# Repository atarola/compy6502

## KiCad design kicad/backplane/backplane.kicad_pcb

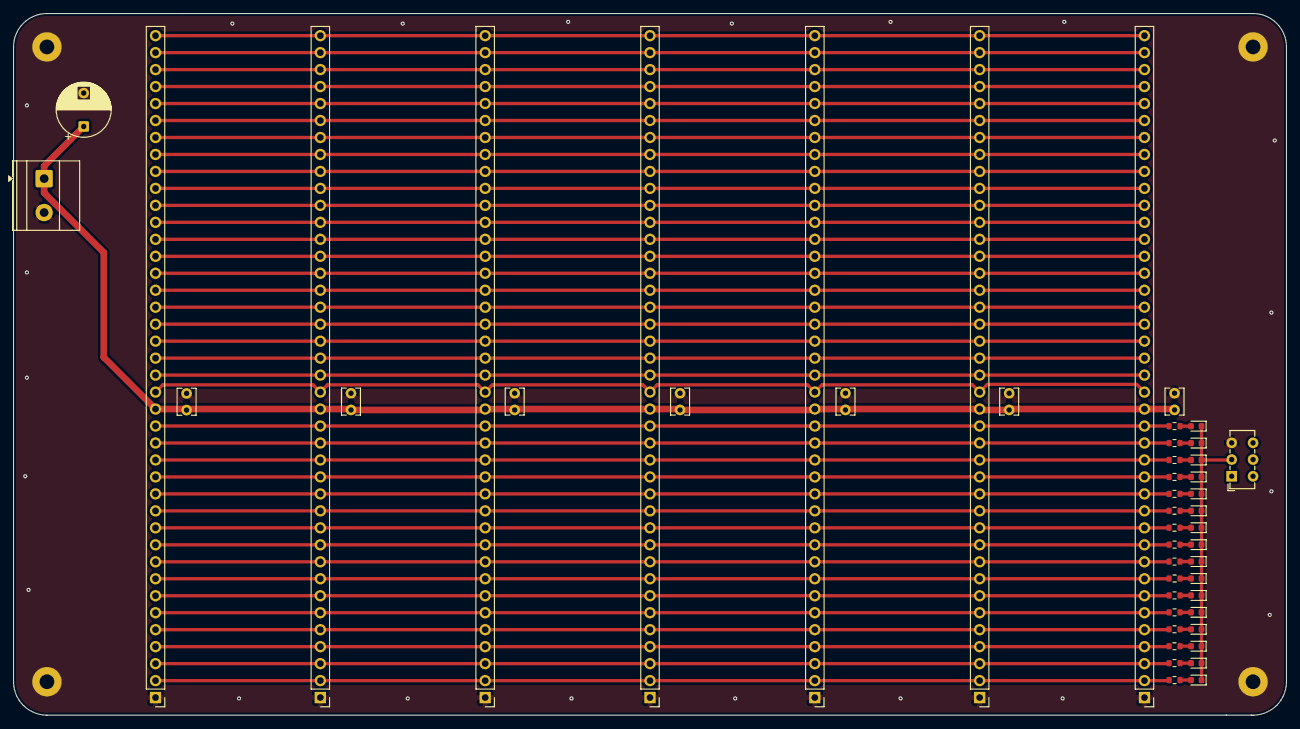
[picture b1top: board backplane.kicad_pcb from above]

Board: 2 copper layers, 190.5 x 105.0 mm, 53 parts (0 on the bottom side), 57 nets.

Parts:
C1: 100u; CP_Radial_D8.0mm_P5.00mm
C2, C3, C4, C5, C6, C7, C8: 0.1u; C_Disc_D3.8mm_W2.6mm_P2.50mm
D1, D2, D3, D4, D5, D6, D7, D8, D9, D10, D11, D12, D13, D14, D15, D16: LED_0603_1608Metric
H1, H2, H3, H4: MountingHole_Pad; MountingHole_2.2mm_M2_Pad
J1, J2, J3, J4, J5, J6, J7: Board Connector; PinHeader_1x40_P2.54mm_Vertical
J9: Screw_Terminal_01x02; TerminalBlock_Phoenix_MKDS-1,5-2-5.08_1x02_P5.08mm_Horizont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
R1, R2, R3, R4, R5, R6, R7, R8, R9, R10, R11, R12, R13, R14, R15, R16: 10k; R_0603_1608Metric
SW1: SW_SPDT; SW_E-Switch_EG1271_SPDT

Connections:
5V: C1.1, C2.1, C3.1, C4.1, C5.1, C6.1, C7.1, C8.1, J1.18, J2.18, J3.18, J4.18, J5.18, J6.18, J7.18, J9.1
/LED_GND: D1.1 (K), D2.1 (K), D3.1 (K), D4.1 (K), D5.1 (K), D6.1 (K), D7.1 (K), D8.1 (K), D9.1 (K), D10.1 (K), D11.1 (K), D12.1 (K), D13.1 (K), D14.1 (K), D15.1 (K), D16.1 (K), SW1.2 (B)
A0: J1.17, J2.17, J3.17, J4.17, J5.17, J6.17, J7.17, R16.1
A1: J1.16, J2.16, J3.16, J4.16, J5.16, J6.16, J7.16, R15.1
A2: J1.15, J2.15, J3.15, J4.15, J5.15, J6.15, J7.15, R14.1
A3: J1.14, J2.14, J3.14, J4.14, J5.14, J6.14, J7.14, R13.1
A4: J1.13, J2.13, J3.13, J4.13, J5.13, J6.13, J7.13, R12.1
A5: J1.12, J2.12, J3.12, J4.12, J5.12, J6.12, J7.12, R11.1
A6: J1.11, J2.11, J3.11, J4.11, J5.11, J6.11, J7.11, R10.1
A7: J1.10, J2.10, J3.10, J4.10, J5.10, J6.10, J7.10, R9.1
A8: J1.9, J2.9, J3.9, J4.9, J5.9, J6.9, J7.9, R8.1
A9: J1.8, J2.8, J3.8, J4.8, J5.8, J6.8, J7.8, R7.1
A10: J1.7, J2.7, J3.7, J4.7, J5.7, J6.7, J7.7, R6.1
A11: J1.6, J2.6, J3.6, J4.6, J5.6, J6.6, J7.6, R5.1
A12: J1.5, J2.5, J3.5, J4.5, J5.5, J6.5, J7.5, R4.1
A13: J1.4, J2.4, J3.4, J4.4, J5.4, J6.4, J7.4, R3.1
A14: J1.3, J2.3, J3.3, J4.3, J5.3, J6.3, J7.3, R2.1
A15: J1.2, J2.2, J3.2, J4.2, J5.2, J6.2, J7.2, R1.1
D0: J1.40, J2.40, J3.40, J4.40, J5.40, J6.40, J7.40
D1: J1.39, J2.39, J3.39, J4.39, J5.39, J6.39, J7.39
D2: J1.38, J2.38, J3.38, J4.38, J5.38, J6.38, J7.38
D3: J1.37, J2.37, J3.37, J4.37, J5.37, J6.37, J7.37
D4: J1.36, J2.36, J3.36, J4.36, J5.36, J6.36, J7.36
D5: J1.35, J2.35, J3.35, J4.35, J5.35, J6.35, J7.35
D6: J1.34, J2.34, J3.34, J4.34, J5.34, J6.34, J7.34
D7: J1.33, J2.33, J3.33, J4.33, J5.33, J6.33, J7.33
GND: C1.2, C2.2, C3.2, C4.2, C5.2, C6.2, C7.2, C8.2, H1.1 (1_1), H2.1 (1_1), H3.1 (1_1), H4.1 (1_1), J1.1, J2.1, J3.1, J4.1, J5.1, J6.1, J7.1, J9.2, SW1.3 (C)
IO0B: J1.24, J2.24, J3.24, J4.24, J5.24, J6.24, J7.24
IO1B: J1.25, J2.25, J3.25, J4.25, J5.25, J6.25, J7.25
IO2B: J1.26, J2.26, J3.26, J4.26, J5.26, J6.26, J7.26
IO3B: J1.27, J2.27, J3.27, J4.27, J5.27, J6.27, J7.27
IORDB: J1.29, J2.29, J3.29, J4.29, J5.29, J6.29, J7.29
IOWRB: J1.28, J2.28, J3.28, J4.28, J5.28, J6.28, J7.28
IRQB: J1.19, J2.19, J3.19, J4.19, J5.19, J6.19, J7.19
MRDB: J1.31, J2.31, J3.31, J4.31, J5.31, J6.31, J7.31
MWRB: J1.30, J2.30, J3.30, J4.30, J5.30, J6.30, J7.30
NMIB: J1.20, J2.20, J3.20, J4.20, J5.20, J6.20, J7.20
unnamed: D1.2 (A), R1.2
unnamed: D2.2 (A), R2.2
unnamed: D3.2 (A), R3.2
unnamed: D4.2 (A), R4.2
unnamed: D5.2 (A), R5.2
unnamed: D6.2 (A), R6.2
unnamed: D7.2 (A), R7.2
unnamed: D8.2 (A), R8.2
unnamed: D9.2 (A), R9.2
unnamed: D10.2 (A), R10.2
unnamed: D11.2 (A), R11.2
unnamed: D12.2 (A), R12.2
unnamed: D13.2 (A), R13.2
unnamed: D14.2 (A), R14.2
unnamed: D15.2 (A), R15.2
unnamed: D16.2 (A), R16.2
PHI1: J1.23, J2.23, J3.23, J4.23, J5.23, J6.23, J7.23
RESB: J1.21, J2.21, J3.21, J4.21, J5.21, J6.21, J7.21
ROMB: J1.32, J2.32, J3.32, J4.32, J5.32, J6.32, J7.32
R/W: J1.22, J2.22, J3.22, J4.22, J5.22, J6.22, J7.22

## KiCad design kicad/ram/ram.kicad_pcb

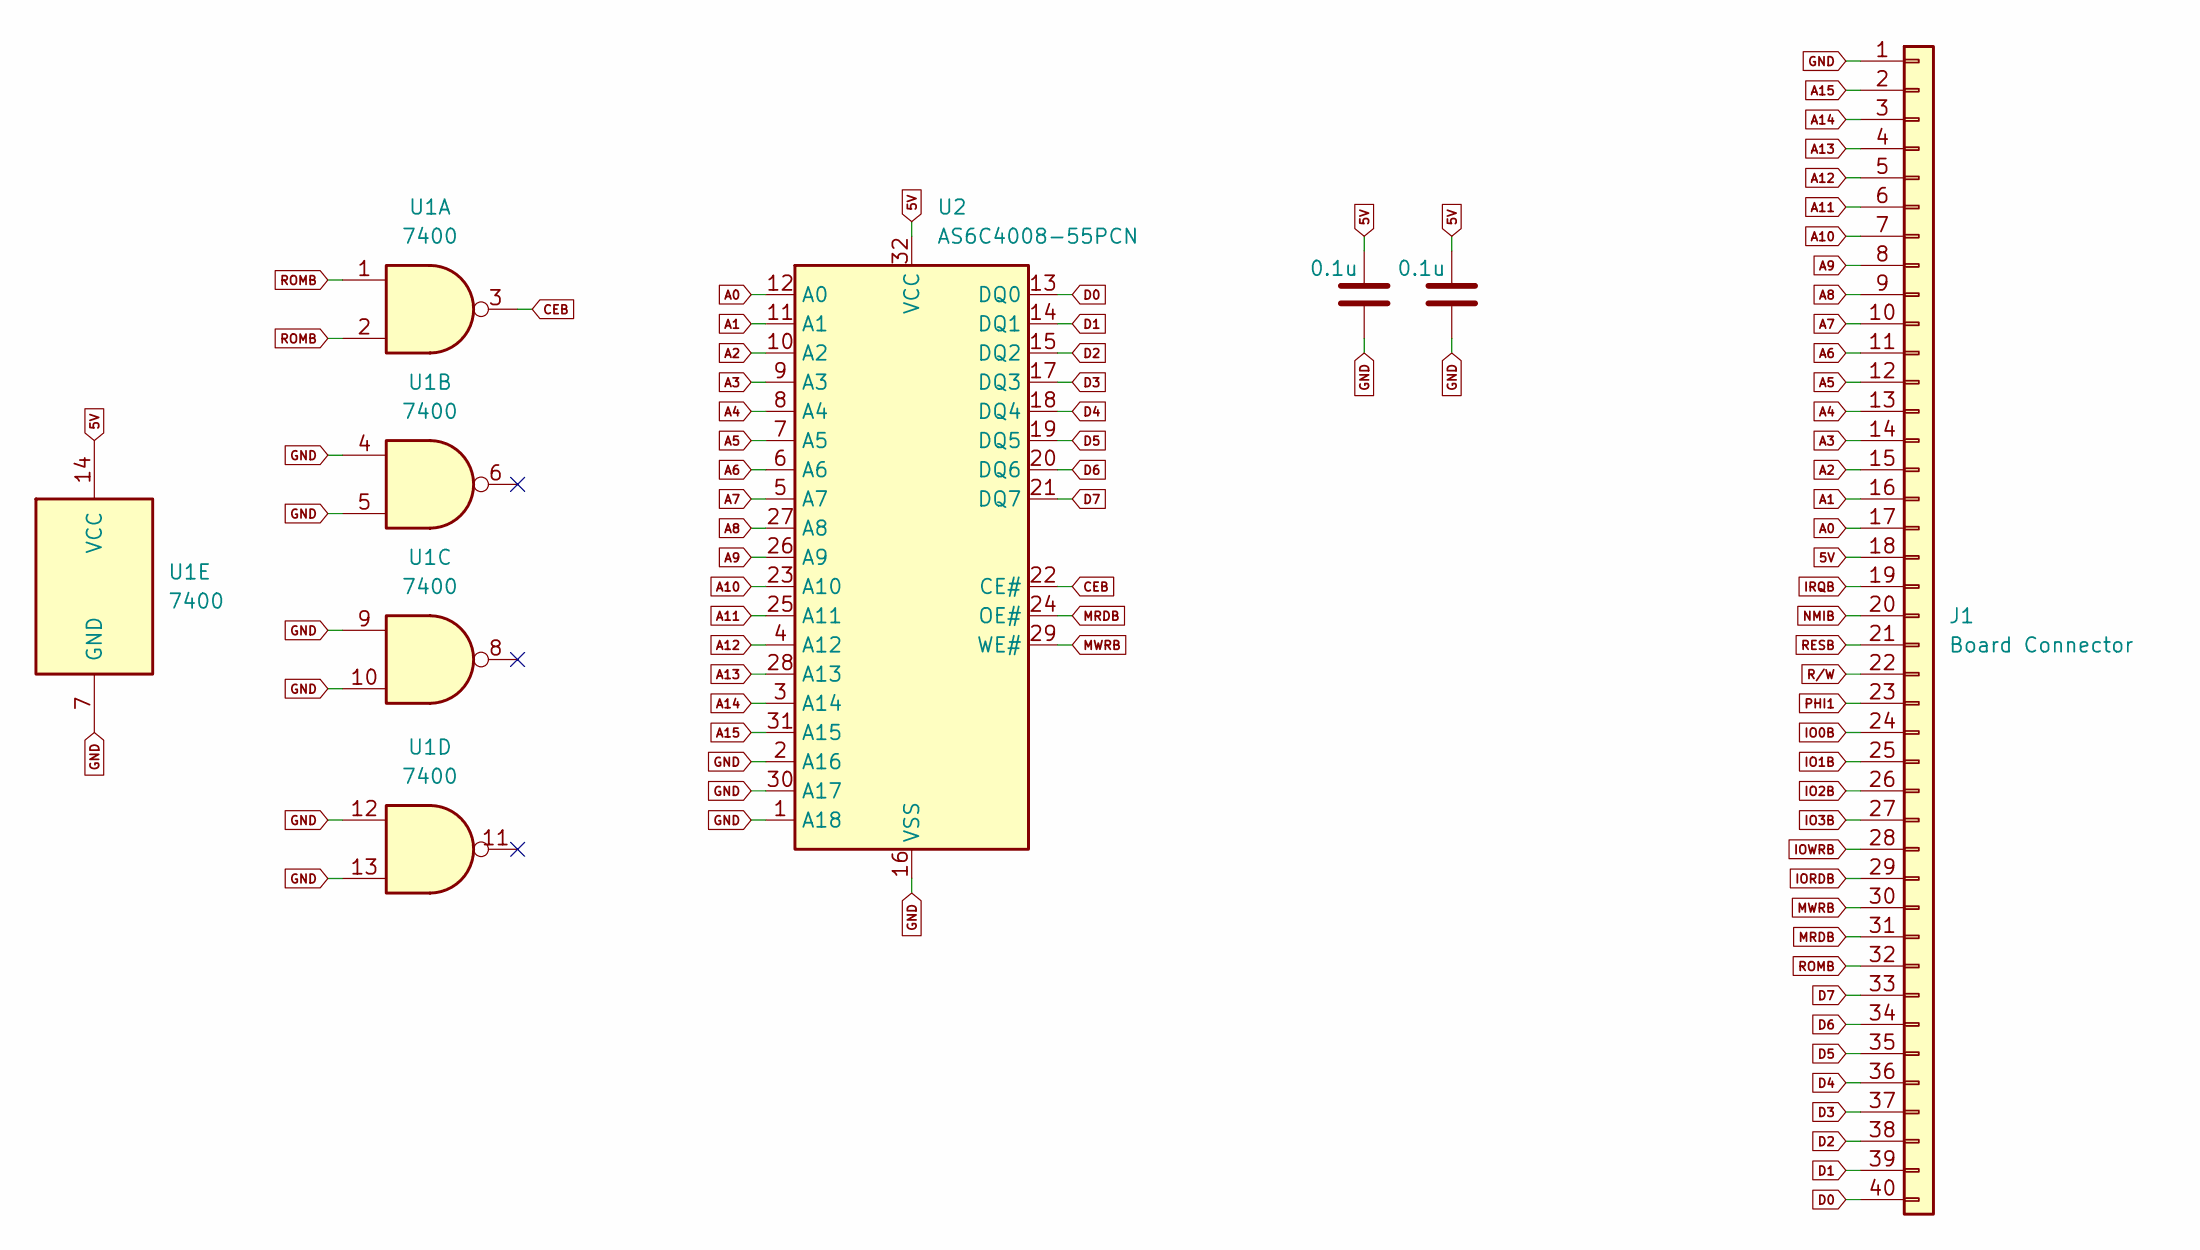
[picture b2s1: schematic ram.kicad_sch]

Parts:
C2, C3: 0.1u; C_Disc_D3.0mm_W1.6mm_P2.50mm
J1: Board Connector; PinHeader_1x40_P2.54mm_Horizontal
U1: 7400; DIP-14_W7.62mm_Socket
U2: AS6C4008-55PCN; DIP-32_W15.24mm_Socket

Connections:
5V: C2.1, C3.1, J1.18, U1.14 (VCC), U2.32 (VCC)
A0: J1.17, U2.12 (A0)
A1: J1.16, U2.11 (A1)
A2: J1.15, U2.10 (A2)
A3: J1.14, U2.9 (A3)
A4: J1.13, U2.8 (A4)
A5: J1.12, U2.7 (A5)
A6: J1.11, U2.6 (A6)
A7: J1.10, U2.5 (A7)
A8: J1.9, U2.27 (A8)
A9: J1.8, U2.26 (A9)
A10: J1.7, U2.23 (A10)
A11: J1.6, U2.25 (A11)
A12: J1.5, U2.4 (A12)
A13: J1.4, U2.28 (A13)
A14: J1.3, U2.3 (A14)
A15: J1.2, U2.31 (A15)
CEB: U1.3, U2.22 (CE#)
D0: J1.40, U2.13 (DQ0)
D1: J1.39, U2.14 (DQ1)
D2: J1.38, U2.15 (DQ2)
D3: J1.37, U2.17 (DQ3)
D4: J1.36, U2.18 (DQ4)
D5: J1.35, U2.19 (DQ5)
D6: J1.34, U2.20 (DQ6)
D7: J1.33, U2.21 (DQ7)
GND: C2.2, C3.2, J1.1, U1.4, U1.5, U1.7 (GND), U1.9, U1.10, U1.12, U1.13, U2.1 (A18), U2.2 (A16), U2.16 (VSS), U2.30 (A17)
IO0B: J1.24
IO1B: J1.25
IO2B: J1.26
IO3B: J1.27
IORDB: J1.29
IOWRB: J1.28
IRQB: J1.19
MRDB: J1.31, U2.24 (OE#)
MWRB: J1.30, U2.29 (WE#)
NMIB: J1.20
PHI1: J1.23
RESB: J1.21
ROMB: J1.32, U1.1, U1.2
R/W: J1.22

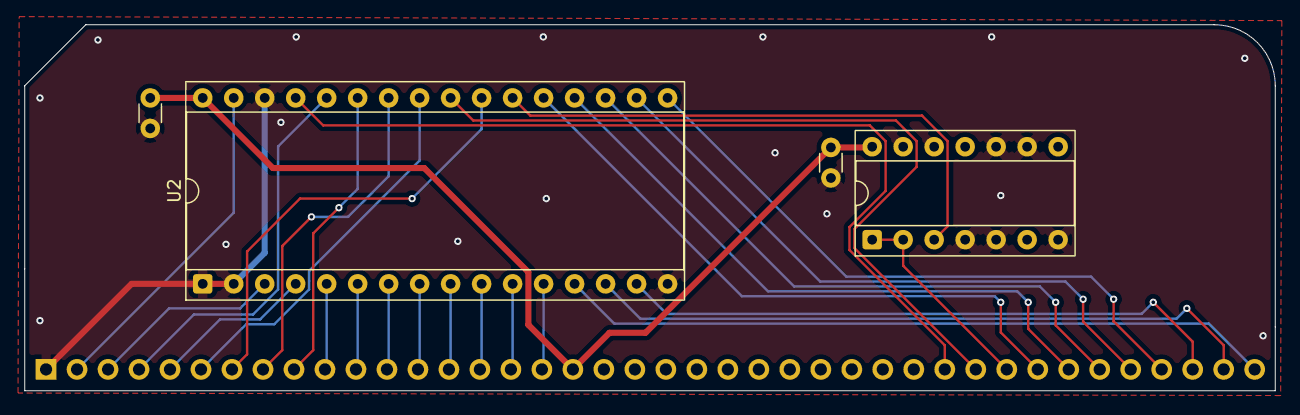
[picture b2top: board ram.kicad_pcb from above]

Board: 2 copper layers, 102.5 x 30.0 mm, 5 parts (1 on the bottom side), 30 nets.
